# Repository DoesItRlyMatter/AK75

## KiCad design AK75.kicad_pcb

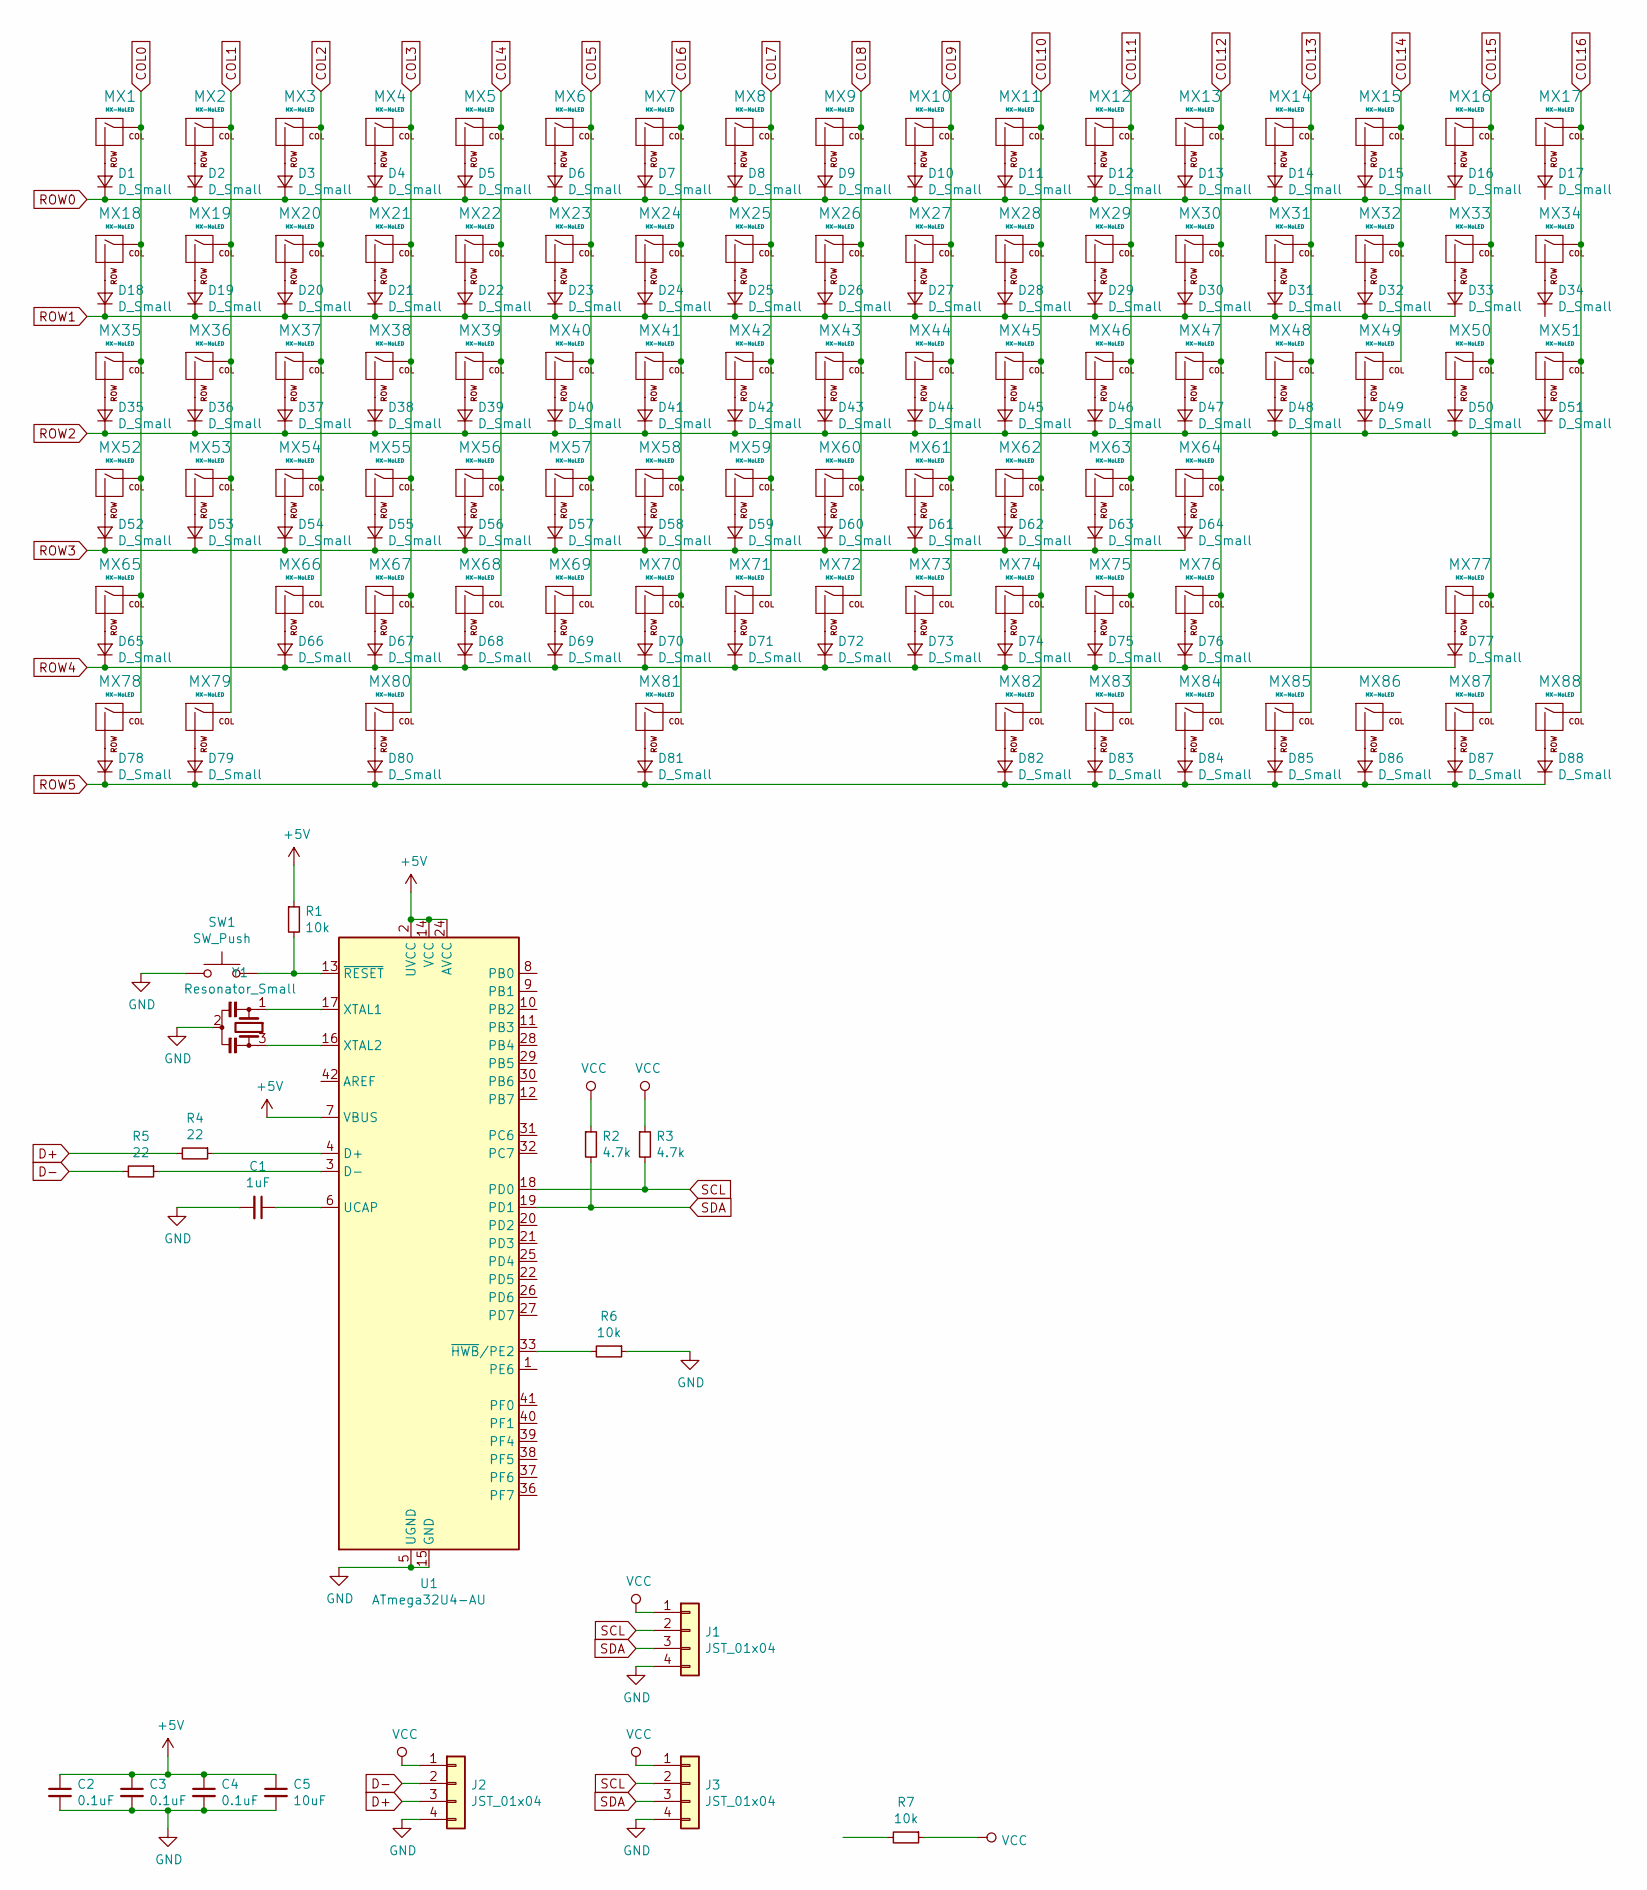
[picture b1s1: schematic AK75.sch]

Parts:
C1: 1uF; C_0805_2012Metric
C2, C3, C4: 0.1uF; C_0805_2012Metric
C5: 10uF; C_0805_2012Metric
D1, D2, D3, D4, D5, D6, D7, D8, D9, D10, D11, D12, D13, D14, D15, D16, D17, D18, D19, D20, D21, D22, D23, D24, D25, D26, D27, D28, D29, D30, D31, D32, D33, D34, D35, D36, D37, D38, D39, D40, D41, D42, D43, D44, D45, D46, D47, D48, D49, D50, D51, D52, D53, D54, D55, D56, D57, D58, D59, D60, D61, D62, D63, D64, D65, D66, D67, D68, D69, D70, D71, D72, D73, D74, D75, D76, D77, D78, D79, D80, D81, D82, D83, D84, D85, D86, D87, D88: D_Small; D_SOD-123-Pretty
J1, J2, J3: JST_01x04; JST-SR-4
MX1, MX2, MX3, MX4, MX5, MX6, MX7, MX8, MX9, MX10, MX11, MX12, MX13, MX14, MX15, MX16, MX17, MX18, MX19, MX20, MX21, MX22, MX23, MX24, MX25, MX26, MX27, MX28, MX29, MX30, MX32, MX33, MX34, MX36, MX37, MX38, MX39, MX40, MX41, MX42, MX43, MX44, MX45, MX46, MX47, MX49, MX50, MX51, MX53, MX54, MX55, MX56, MX57, MX58, MX59, MX60, MX61, MX62, MX63, MX66, MX67, MX68, MX69, MX70, MX71, MX72, MX73, MX74, MX75, MX77, MX86, MX87, MX88: MX-NoLED; MXOnly-1U-NoLED
MX31: MX-NoLED; MXOnly-2U-NoLED
MX35, MX48: MX-NoLED; MXOnly-1.5U-NoLED
MX52: MX-NoLED; MXOnly-1.75U-NoLED
MX64, MX65: MX-NoLED; MXOnly-2.25U-NoLED
MX76: MX-NoLED; MXOnly-2.75U-NoLED
MX78, MX79, MX80, MX82, MX83, MX84, MX85: MX-NoLED; MXOnly-1.25U-NoLED
MX81: MX-NoLED; MXOnly-6.25U-ReversedStabilizers-NoLED
R1, R6, R7: 10k; R_0805_2012Metric
R2, R3: 4.7k; R_0805_2012Metric
R4, R5: 22; R_0805_2012Metric
SW1: SW_Push; SKQG-1155865
U1: ATmega32U4-AU; TQFP-44_10x10mm_P0.8mm
Y1: Resonator_Small; CSTCE

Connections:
+5V: C2.1, C3.1, C4.1, C5.1, R1.1, U1.2 (UVCC), U1.7 (VBUS), U1.14 (VCC), U1.24 (AVCC), U1.34 (VCC), U1.44 (AVCC)
COL0: MX1.1 (COL), MX18.1 (COL), MX35.1 (COL), MX52.1 (COL), MX65.1 (COL), MX78.1 (COL)
COL1: MX2.1 (COL), MX19.1 (COL), MX36.1 (COL), MX53.1 (COL), MX79.1 (COL)
COL2: MX3.1 (COL), MX20.1 (COL), MX37.1 (COL), MX54.1 (COL), MX66.1 (COL)
COL3: MX4.1 (COL), MX21.1 (COL), MX38.1 (COL), MX55.1 (COL), MX67.1 (COL), MX80.1 (COL)
COL4: MX5.1 (COL), MX22.1 (COL), MX39.1 (COL), MX56.1 (COL), MX68.1 (COL)
COL5: MX6.1 (COL), MX23.1 (COL), MX40.1 (COL), MX57.1 (COL), MX69.1 (COL)
COL6: MX7.1 (COL), MX24.1 (COL), MX41.1 (COL), MX58.1 (COL), MX70.1 (COL), MX81.1 (COL)
COL7: MX8.1 (COL), MX25.1 (COL), MX42.1 (COL), MX59.1 (COL), MX71.1 (COL)
COL8: MX9.1 (COL), MX26.1 (COL), MX43.1 (COL), MX60.1 (COL), MX72.1 (COL)
COL9: MX10.1 (COL), MX27.1 (COL), MX44.1 (COL), MX61.1 (COL), MX73.1 (COL)
COL10: MX11.1 (COL), MX28.1 (COL), MX45.1 (COL), MX62.1 (COL), MX74.1 (COL), MX82.1 (COL)
COL11: MX12.1 (COL), MX29.1 (COL), MX46.1 (COL), MX63.1 (COL), MX75.1 (COL), MX83.1 (COL)
COL12: MX13.1 (COL), MX30.1 (COL), MX47.1 (COL), MX64.1 (COL), MX76.1 (COL), MX84.1 (COL)
COL13: MX14.1 (COL), MX31.1 (COL), MX48.1 (COL), MX85.1 (COL)
COL14: MX15.1 (COL), MX32.1 (COL), MX49.1 (COL)
COL15: MX16.1 (COL), MX33.1 (COL), MX50.1 (COL), MX77.1 (COL), MX87.1 (COL)
COL16: MX17.1 (COL), MX34.1 (COL), MX51.1 (COL), MX88.1 (COL)
D+: J2.3, R4.2
D-: J2.2, R5.2
GND: C1.2, C2.2, C3.2, C4.2, C5.2, J1.4, J2.4, J3.4, R6.1, SW1.1, U1.5 (UGND), U1.15 (GND), U1.23 (GND), U1.35 (GND), U1.43 (GND), Y1.2
unnamed: C1.1, U1.6 (UCAP)
unnamed: D1.2 (A), MX1.2 (ROW)
unnamed: D2.2 (A), MX2.2 (ROW)
unnamed: D3.2 (A), MX3.2 (ROW)
unnamed: D4.2 (A), MX4.2 (ROW)
unnamed: D5.2 (A), MX5.2 (ROW)
unnamed: D6.2 (A), MX6.2 (ROW)
unnamed: D7.2 (A), MX7.2 (ROW)
unnamed: D8.2 (A), MX8.2 (ROW)
unnamed: D9.2 (A), MX9.2 (ROW)
unnamed: D10.2 (A), MX10.2 (ROW)
unnamed: D11.2 (A), MX11.2 (ROW)
unnamed: D12.2 (A), MX12.2 (ROW)
unnamed: D13.2 (A), MX13.2 (ROW)
unnamed: D14.2 (A), MX14.2 (ROW)
unnamed: D15.2 (A), MX15.2 (ROW)
unnamed: D16.2 (A), MX16.2 (ROW)
unnamed: D17.2 (A), MX17.2 (ROW)
unnamed: D18.2 (A), MX18.2 (ROW)
unnamed: D19.2 (A), MX19.2 (ROW)
unnamed: D20.2 (A), MX20.2 (ROW)
unnamed: D21.2 (A), MX21.2 (ROW)
unnamed: D22.2 (A), MX22.2 (ROW)
unnamed: D23.2 (A), MX23.2 (ROW)
unnamed: D24.2 (A), MX24.2 (ROW)
unnamed: D25.2 (A), MX25.2 (ROW)
unnamed: D26.2 (A), MX26.2 (ROW)
unnamed: D27.2 (A), MX27.2 (ROW)
unnamed: D28.2 (A), MX28.2 (ROW)
unnamed: D29.2 (A), MX29.2 (ROW)
unnamed: D30.2 (A), MX30.2 (ROW)
unnamed: D31.2 (A), MX31.2 (ROW)
unnamed: D32.2 (A), MX32.2 (ROW)
unnamed: D33.2 (A), MX33.2 (ROW)
unnamed: D34.2 (A), MX34.2 (ROW)
unnamed: D35.2 (A), MX35.2 (ROW)
unnamed: D36.2 (A), MX36.2 (ROW)
unnamed: D37.2 (A), MX37.2 (ROW)
unnamed: D38.2 (A), MX38.2 (ROW)
unnamed: D39.2 (A), MX39.2 (ROW)
unnamed: D40.2 (A), MX40.2 (ROW)
unnamed: D41.2 (A), MX41.2 (ROW)
unnamed: D42.2 (A), MX42.2 (ROW)
unnamed: D43.2 (A), MX43.2 (ROW)
unnamed: D44.2 (A), MX44.2 (ROW)
unnamed: D45.2 (A), MX45.2 (ROW)
unnamed: D46.2 (A), MX46.2 (ROW)
unnamed: D47.2 (A), MX47.2 (ROW)
unnamed: D48.2 (A), MX48.2 (ROW)
unnamed: D49.2 (A), MX49.2 (ROW)
unnamed: D50.2 (A), MX50.2 (ROW)
unnamed: D51.2 (A), MX51.2 (ROW)
unnamed: D52.2 (A), MX52.2 (ROW)
unnamed: D53.2 (A), MX53.2 (ROW)
unnamed: D54.2 (A), MX54.2 (ROW)
unnamed: D55.2 (A), MX55.2 (ROW)
unnamed: D56.2 (A), MX56.2 (ROW)
unnamed: D57.2 (A), MX57.2 (ROW)
unnamed: D58.2 (A), MX58.2 (ROW)
unnamed: D59.2 (A), MX59.2 (ROW)
unnamed: D60.2 (A), MX60.2 (ROW)
unnamed: D61.2 (A), MX61.2 (ROW)
unnamed: D62.2 (A), MX62.2 (ROW)
unnamed: D63.2 (A), MX63.2 (ROW)
unnamed: D64.2 (A), MX64.2 (ROW)
unnamed: D65.2 (A), MX65.2 (ROW)
unnamed: D66.2 (A), MX66.2 (ROW)
unnamed: D67.2 (A), MX67.2 (ROW)
unnamed: D68.2 (A), MX68.2 (ROW)
unnamed: D69.2 (A), MX69.2 (ROW)
unnamed: D70.2 (A), MX70.2 (ROW)
unnamed: D71.2 (A), MX71.2 (ROW)
unnamed: D72.2 (A), MX72.2 (ROW)
unnamed: D73.2 (A), MX73.2 (ROW)
unnamed: D74.2 (A), MX74.2 (ROW)
unnamed: D75.2 (A), MX75.2 (ROW)
unnamed: D76.2 (A), MX76.2 (ROW)
unnamed: D77.2 (A), MX77.2 (ROW)
unnamed: D78.2 (A), MX78.2 (ROW)
unnamed: D79.2 (A), MX79.2 (ROW)
unnamed: D80.2 (A), MX80.2 (ROW)
unnamed: D81.2 (A), MX81.2 (ROW)
unnamed: D82.2 (A), MX82.2 (ROW)
unnamed: D83.2 (A), MX83.2 (ROW)
unnamed: D84.2 (A), MX84.2 (ROW)
unnamed: D85.2 (A), MX85.2 (ROW)
unnamed: D86.2 (A), MX86.2 (ROW)
unnamed: D87.2 (A), MX87.2 (ROW)
unnamed: D88.2 (A), MX88.2 (ROW)
unnamed: R1.2, SW1.2, U1.13 (~RESET)
unnamed: R4.1, U1.4 (D+)
unnamed: R5.1, U1.3 (D-)
unnamed: R6.2, U1.33 (~HWB~/PE2)
unnamed: U1.16 (XTAL2), Y1.3
unnamed: U1.17 (XTAL1), Y1.1
ROW0: D1.1 (K), D2.1 (K), D3.1 (K), D4.1 (K), D5.1 (K), D6.1 (K), D7.1 (K), D8.1 (K), D9.1 (K), D10.1 (K), D11.1 (K), D12.1 (K), D13.1 (K), D14.1 (K), D15.1 (K), D16.1 (K)
ROW1: D18.1 (K), D19.1 (K), D20.1 (K), D21.1 (K), D22.1 (K), D23.1 (K), D24.1 (K), D25.1 (K), D26.1 (K), D27.1 (K), D28.1 (K), D29.1 (K), D30.1 (K), D31.1 (K), D32.1 (K), D33.1 (K)
ROW2: D35.1 (K), D36.1 (K), D37.1 (K), D38.1 (K), D39.1 (K), D40.1 (K), D41.1 (K), D42.1 (K), D43.1 (K), D44.1 (K), D45.1 (K), D46.1 (K), D47.1 (K), D48.1 (K), D49.1 (K), D50.1 (K), D51.1 (K)
ROW3: D52.1 (K), D53.1 (K), D54.1 (K), D55.1 (K), D56.1 (K), D57.1 (K), D58.1 (K), D59.1 (K), D60.1 (K), D61.1 (K), D62.1 (K), D63.1 (K), D64.1 (K)
ROW4: D65.1 (K), D66.1 (K), D67.1 (K), D68.1 (K), D69.1 (K), D70.1 (K), D71.1 (K), D72.1 (K), D73.1 (K), D74.1 (K), D75.1 (K), D76.1 (K), D77.1 (K)
ROW5: D78.1 (K), D79.1 (K), D80.1 (K), D81.1 (K), D82.1 (K), D83.1 (K), D84.1 (K), D85.1 (K), D86.1 (K), D87.1 (K), D88.1 (K)
SCL: J1.2, J3.2, R3.2, U1.18 (PD0)
SDA: J1.3, J3.3, R2.2, U1.19 (PD1)
VCC: J1.1, J2.1, J3.1, R2.1, R3.1, R7.1

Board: 2 copper layers, 194 parts (105 on the bottom side), 125 nets, no tracks yet.

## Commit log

2020-07-05 created projekt
2020-07-05 added submodules
2020-07-05 added footprint libraries
2020-07-05 completed controller, matrix and usb sch
2020-07-05 assigned footprints and added footprint for resonator
2020-07-05 updated switch matrix to TKL in sch
2020-07-05 assigned footprints for components
2020-07-05 placed switches on pcb
2020-07-06 sorted components
2020-07-06 initial diode placement
